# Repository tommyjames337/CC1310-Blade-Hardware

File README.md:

# CC1310-Blade-Hardware README

This repository contains the crucial design files for the CC1310 Blade (Rev D). Note that the Rev D board is functionally
identical to the Rev C board. It will work with all CC1310 Blade Rev C demo projects.

The files in this project should be organized accordingly in order to open the project correctly in KiCad:

1) Place CC1310_Dev_Board_D into desired directory.

2) Stock.zip and CC1310.zip should be unpacked into the same directory that CC1310_Dev_Board_D was placed into.

After the project is correctly opened, you may have to correct the references to the footprint and schematic symbol files. Once these references are corrected, you may create gerber files and order PCBs from your favorite manufacturer.

The repository for CC1310 Blade software demos can be found here: https://github.com/mprost/CC1310-Blade-Demos

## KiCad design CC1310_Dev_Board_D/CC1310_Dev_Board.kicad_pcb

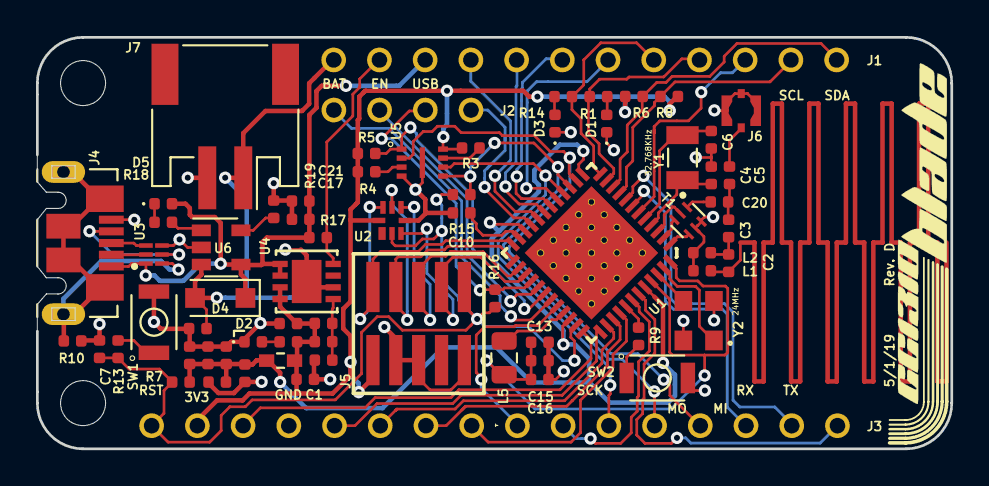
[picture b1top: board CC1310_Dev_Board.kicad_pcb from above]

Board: 2 copper layers, 50.8 x 22.9 mm, 71 parts (1 on the bottom side), 69 nets.

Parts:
C1: 0.1uF; C_0402_1005Metric
C2: 3.3pF; C_0402_1005Metric
C3: DNM_0402; C_0402_1005Metric
C4, C6: 12pF; C_0402_1005Metric
C5: 330pF; C_0402_1005Metric
C7, C8, C9, C11, C14, C15, C16: 100nF; C_0402_1005Metric
C10: 1uF; C_0402_1005Metric
C12, C13: 22uF; C_0402_1005Metric
C17, C19: 2.2uF; C_0402_1005Metric
C18: 15pF; C_0402_1005Metric
C20: 100pF; C_0402_1005Metric
C21, C22: 10uF; C_0402_1005Metric
D1: SML-P12U2TT86R; LED_0402_1005Metric
D2, D3: SML-P13PTT86R; LED_0402_1005Metric
D4: MBR120; D_SOD-123F
D5: SML-P12DTT86R; LED_0402_1005Metric
J1: 68685-312LF; 68685-312LF-BLADE
J2: 68685-304LF; 68685-304LF-BLADE
J3: 68685-316LF; 68685-316LF-BLADE
J4: 105164-0001; MOLEX_105164-0001
J5: SAMTEC-FTSH-105-01-X-DV
J6: MM5829-2700RJ4; MURATA_MM5829-2700RJ4
J7: JST-PH; JST_PH_S2B-PH-SM4-TB_1x02-1MP_P2.00mm_Horizontal
J8: SMTU1220-LF; SMTU1225LF
L1: 18nH; L_0402_1005Metric
L2: DNM; L_0402_1005Metric
L4: BLM18HE152SN1D; INDC1608X95
L5: 6.8µH; L_0805_2012Metric
MH1, MH2: MountingHole; MountingHole_2.5mm
R1, R2, R14: 180; R_0402_1005Metric
R3, R4: DNI; R_0402_1005Metric
R5: 2.2K; R_0402_1005Metric
R6, R8: 3.3K; R_0402_1005Metric
R7, R10, R17: 100K; R_0402_1005Metric
R9, R13: 100; R_0402_1005Metric
R11: 51K; R_0402_1005Metric
R12: 30K; R_0402_1005Metric
R15, R16: 0; R_0402_1005Metric
R18: 274; R_0402_1005Metric
R19: 10K; R_0402_1005Metric
SW1, SW2: B3U-1000P; SW_B3U-1000P
T1: 0850BM14E0016T; INDCAF50P160X80X70-6N
U1: CC1310F64RGZT; QFN50P700X700X100-49N
U2: TPD6E004RSER
U3: TPD4E004DRYR
U4: TPS79601DRBR
U5: MX25R8035FZUIL0; USON-8L
U6: MCP73831T-2ACI_OT; SOT-23-5
Y1: FC-135R_32.7680KA-AG0; XTAL_FC-135R_32.7680KA-AG0
Y2: 24MHz; OSCSC320X250X100N

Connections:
AIO_23: J3.A3, U1.36
AIO_24: J3.A5, U1.37
AIO_25: J3.A6, U1.38
AIO_26: J3.A7, U1.39
AIO_27: J3.A8, U1.40
CC1310_RESET: C7.2, J3.A1, J5.10, R7.1, R13.2, R15.2, R16.2, U1.35, U2.2
CC1310_TCK: J5.4, U1.25, U2.6
CC1310_TMS: J5.2, U1.24, U2.7
CC1310_VDD: C1.1, C18.1, C19.1, J3.A2, J5.1, L4.1, R2.2, R3.1, R4.1, R5.1, R6.2, R8.2, R11.1, U2.8, U4.3, U4.4, U5.8
DIO_1: J1.A10, U1.6
DIO_2_UART_RX: J3.A14, U1.7
DIO_3_UART_TX: J3.A15, U1.8
DIO_4_SCL: J1.A11, R8.1, U1.9
DIO_5_SDA: J1.A12, R6.1, U1.10
DIO_8_MISO: J3.A13, U1.14, U5.2
DIO_9_MOSI: J3.A12, R15.1, U1.15, U5.5
DIO_10_SCLK: J3.A11, U1.16, U5.6
DIO_11: J1.A7, U1.17
DIO_12: J1.A6, U1.18
DIO_13: J1.A5, U1.19
DIO_14: J1.A4, U1.20
DIO_15: J2.A1, U1.21
DIO_16: J5.6, U1.26, U2.5
DIO_17: J5.8, U1.27, U2.3
DIO_18: J2.A2, R16.1, U1.28
DIO_19: J2.A3, U1.29
DIO_20: R5.2, U1.30, U5.1
DIO_21: J2.A4, U1.31
DIO_22: J3.A9, U1.32
DIO_29: J3.A10, U1.42
DIO_30: J3.A16, U1.43
EN: J1.A2, R17.1, U4.8
GND: C1.2, C4.1, C6.1, C7.1, C8.2, C9.2, C10.2, C11.2, C12.2, C13.2, C14.2, C15.2, C16.2, C17.2, C19.2, C21.2, C22.2, D1.1, D2.1, D3.1, J3.A4, J4.5, J5.3, J5.5, J5.9, J6.2, J6.3, J6.4, J7.2, J8.2, L1.2, L2.2, R10.2, R12.2, R19.2, SW1.2, SW2.2, T1.5, T1.6, U1.49, U1.50, U1.51, U1.52, U1.53, U1.54, U1.55, U1.56, U1.57, U1.58, U1.59, U1.60, U1.61, U1.62, U1.63, U1.64, U1.65, U1.66, U1.67, U1.68, U1.69, U1.70, U1.71, U1.72, U1.73, U1.74, U2.4, U3.3, U4.6, U4.9, U5.4, U5.9, U6.2, Y2.2, Y2.4
LED_USER_GREEN: J1.A8, R14.2, U1.12
LED_USER_RED: J1.A9, R1.2, U1.11
unnamed: C2.2, L1.1
unnamed: C2.1, C3.2, L2.1
unnamed: C4.2, U1.4, Y1.1
unnamed: C5.2, J6.1
unnamed: C6.2, U1.5, Y1.2
unnamed: C10.1, U1.23
unnamed: C13.1, C15.1, C16.1, L5.2, U1.45, U1.48
unnamed: C18.2, R11.2, R12.1, U4.5
unnamed: C20.1, T1.1
unnamed: C3.1, C5.1, C20.2
unnamed: D1.2, R1.1
unnamed: D2.2, R2.1
unnamed: D3.2, R14.1
unnamed: D5.1, R18.2
unnamed: J4.2, U3.5
unnamed: J4.3, U3.4
unnamed: J4.4, U3.2
unnamed: J4.SH1, J4.SH2, J4.SH3, J4.SH4, J4.SH5, J4.SH6, R10.1, U3.1
unnamed: L5.1, U1.33
unnamed: R3.2, U5.7
unnamed: R4.2, U5.3
unnamed: R9.1, SW2.1
unnamed: R13.1, SW1.1
unnamed: R18.1, U6.1
unnamed: R19.1, U6.5
unnamed: T1.2, U1.3
unnamed: T1.3, U1.2
unnamed: T1.4, U1.1
unnamed: U1.46, Y2.3
unnamed: U1.47, Y2.1
SW_USER: R9.2, U1.41
VBAT: C22.1, D4.2, J1.A1, J7.1, J8.1, U6.3
VBUS: C17.1, C21.1, D4.1, D5.2, J1.A3, J4.1, R17.2, U3.6, U4.1, U4.2, U6.4
VDD: C8.1, C9.1, C11.1, C12.1, C14.1, L4.2, R7.2, U1.13, U1.22, U1.34, U1.44

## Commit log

2019-05-23 Critical hardware files for CC1310 Blade Rev D
2019-05-23 Create LICENSE

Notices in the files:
parts and their libraries:
Copyright 2016 Accelerated Designs. All rights reserved.
